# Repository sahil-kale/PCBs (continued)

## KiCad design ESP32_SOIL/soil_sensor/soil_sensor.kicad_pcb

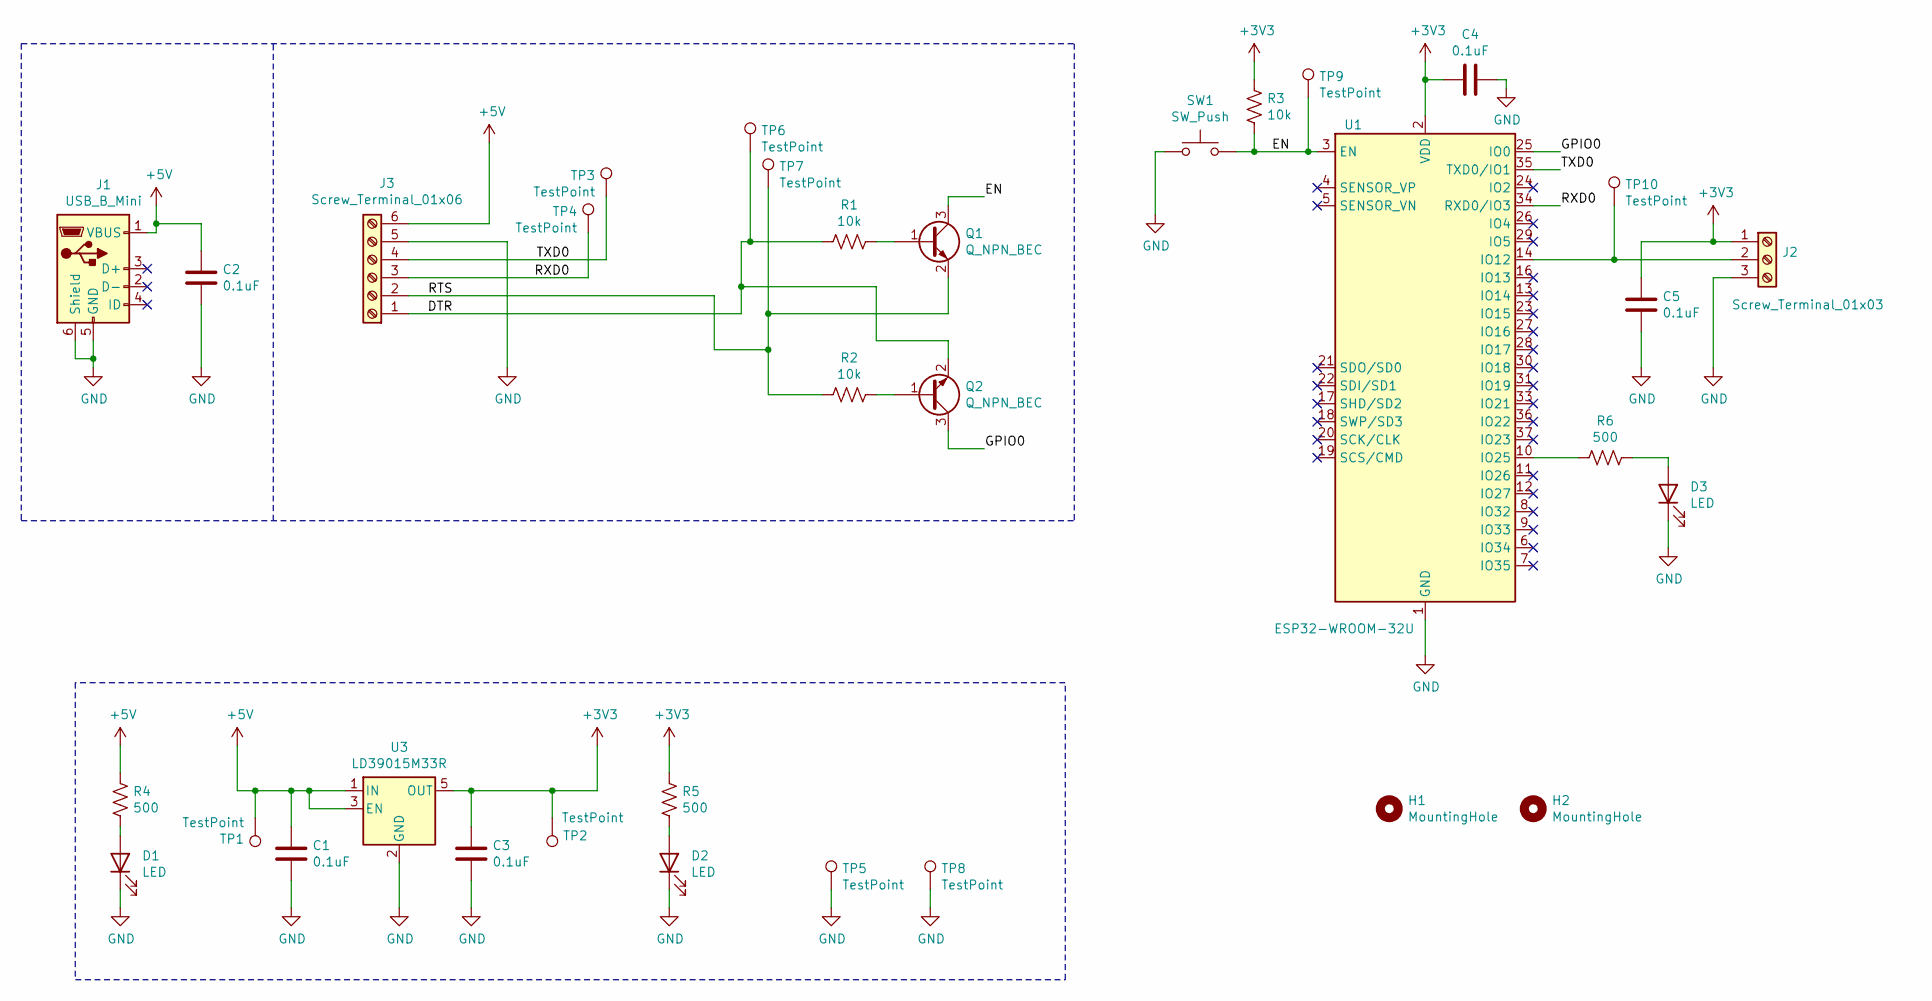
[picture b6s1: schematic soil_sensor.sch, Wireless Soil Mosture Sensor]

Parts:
C1, C2, C3, C4, C5: 0.1uF; C_0603_1608Metric_Pad1.08x0.95mm_HandSolder; Digikey 311-1824-1-ND
D1: LED; LED_0603_1608Metric_Pad1.05x0.95mm_HandSolder; Digikey P14141CT-ND
D2: LED; LED_0603_1608Metric_Pad1.05x0.95mm_HandSolder; Digikey 732-4978-1-ND
D3: LED; LED_0603_1608Metric_Pad1.05x0.95mm_HandSolder; Digikey 732-4980-1-ND
H1, H2: MountingHole; MountingHole_2.1mm
J1: USB_B_Mini; USB_Micro-B_Molex_47346-0001; Digikey WM17141CT-ND
J2: Screw_Terminal_01x03; TerminalBlock_Phoenix_PT-1,5-3-5.0-H_1x03_P5.00mm_Horizontal; Digikey 277-1578-ND
J3: Screw_Terminal_01x06; PinSocket_1x06_P2.54mm_Vertical; Digikey 1849-PR20204VBNN-ND
Q1: Q_NPN_BEC; SOT-23; Digikey 641-1790-1-ND
Q2: Q_NPN_BEC; SOT-23; Digikey FMMTL619TADICT-ND
R1, R2, R3: 10k; R_0603_1608Metric_Pad0.98x0.95mm_HandSolder; Digikey RMCF0603JG10K0CT-ND
R4, R5, R6: 500; R_0603_1608Metric_Pad0.98x0.95mm_HandSolder; Digikey CR0603-FX-7500ELFCT-ND
SW1: SW_Push; SW_PUSH-12mm_Wuerth-430476085716; Digikey 430476085716-ND
TP1, TP2, TP3, TP4, TP5, TP6, TP7, TP8, TP9, TP10: TestPoint; TestPoint_Pad_D1.0mm
U1: ESP32-WROOM-32U; Digikey 1904-1007-1-ND
U3: LD39015M33R; SOT-23-5; Digikey 497-6979-1-ND

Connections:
+3V3: C3.2, C4.2, C5.2, J2.1, R3.1, R5.1, TP2.1, U1.2 (VDD), U3.5 (OUT)
+5V: C1.2, C2.2, J1.1 (VBUS), J3.6, R4.1, TP1.1, U3.1 (IN), U3.3 (EN)
/DTR: J3.1, Q2.2 (E), R1.2, TP6.1
/EN: Q1.3 (C), R3.2, SW1.2, TP9.1, U1.3 (EN)
/GPIO0: Q2.3 (C), U1.25 (IO0)
/RTS: J3.2, Q1.2 (E), R2.2, TP7.1
/RXD0: J3.3, TP4.1, U1.34 (RXD0/IO3)
/TXD0: J3.4, TP3.1, U1.35 (TXD0/IO1)
GND: C1.1, C2.1, C3.1, C4.1, C5.1, D1.1 (K), D2.1 (K), D3.1 (K), J1.5 (GND), J1.6 (Shield), J2.3, J3.5, SW1.1, TP5.1, TP8.1, U1.1 (GND), U1.15 (GND), U1.38 (GND), U1.39 (GND), U3.2 (GND)
unnamed: D1.2 (A), R4.2
unnamed: D2.2 (A), R5.2
unnamed: D3.2 (A), R6.1
unnamed: J2.2, TP10.1, U1.14 (IO12)
unnamed: Q1.1 (B), R1.1
unnamed: Q2.1 (B), R2.1
unnamed: R6.2, U1.10 (IO25)

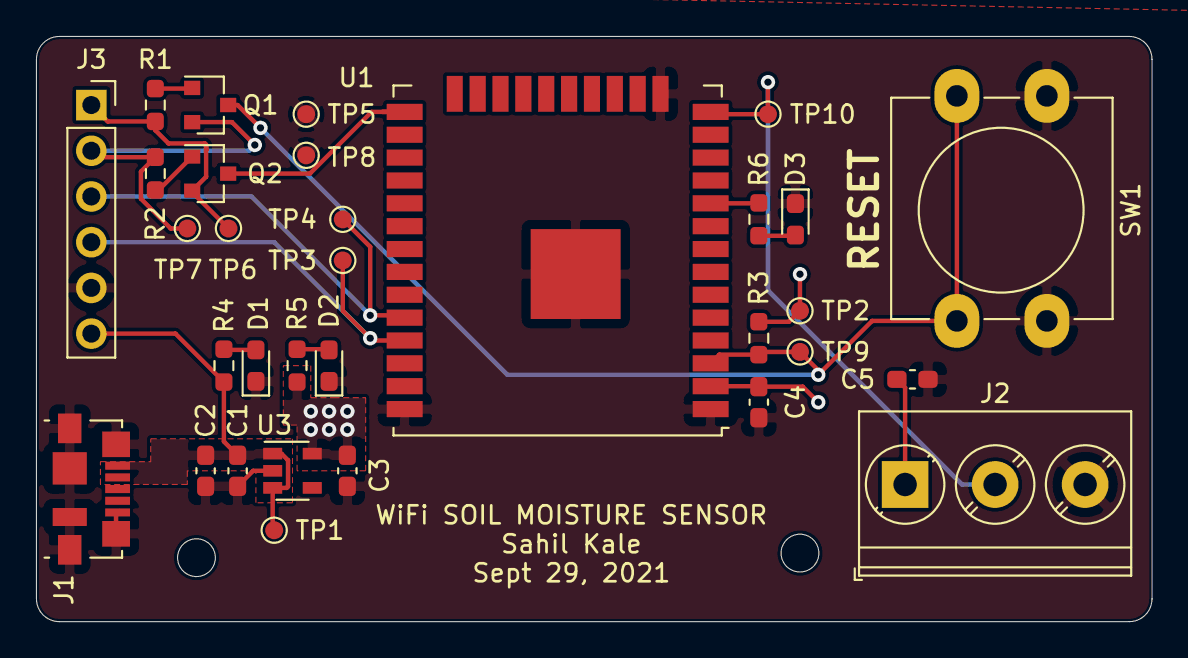
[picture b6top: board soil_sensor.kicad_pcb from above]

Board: 2 copper layers, 62.0 x 32.5 mm, 34 parts (0 on the bottom side), 16 nets.

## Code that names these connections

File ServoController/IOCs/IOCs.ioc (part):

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Mcu.Name=STM32L431C(B-C)Tx
Mcu.Package=LQFP48
Mcu.UserName=STM32L431CCTx
PA0.GPIOParameters=GPIO_Label
PA0.GPIO_Label=CURR_A
PA0.Signal=ADCx_IN5
PA1.GPIOParameters=GPIO_Label
PA1.GPIO_Label=CURR_B
PA1.Signal=ADCx_IN6
PA10.Mode=Asynchronous
PA10.Signal=USART1_RX
PA13\ (JTMS-SWDIO).Mode=Trace_Asynchronous_SW
PA13\ (JTMS-SWDIO).Signal=SYS_JTMS-SWDIO
PA14\ (JTCK-SWCLK).Mode=Trace_Asynchronous_SW
PA14\ (JTCK-SWCLK).Signal=SYS_JTCK-SWCLK
PA5.GPIOParameters=GPIO_Label
PA5.GPIO_Label=PWM_IN
PA5.Signal=S_TIM2_CH1
PA6.GPIOParameters=GPIO_Label
PA6.GPIO_Label=DIR_A
PA6.Signal=GPIO_Output
PA7.GPIOParameters=GPIO_Label
PA7.GPIO_Label=DIR_B
PA7.Signal=GPIO_Output
PA8.GPIOParameters=GPIO_Label
PA8.GPIO_Label=PWM_A
PA8.Signal=S_TIM1_CH1
PA9.GPIOParameters=GPIO_Label
PA9.GPIO_Label=PWM_B
PA9.Signal=S_TIM1_CH2
PB0.GPIOParameters=GPIO_Label
PB0.GPIO_Label=FAULT_A
PB0.Signal=GPIO_Input
PB1.GPIOParameters=GPIO_Label
PB1.GPIO_Label=FAULT_B
PB1.Signal=GPIO_Input
PB10.GPIOParameters=GPIO_Label
PB10.GPIO_Label=SLEEP_B
PB10.Signal=GPIO_Output
PB12.GPIOParameters=GPIO_Label
PB12.GPIO_Label=BRAKE_A
PB12.Signal=GPIO_Output
PB13.GPIOParameters=GPIO_Label
PB13.GPIO_Label=BRAKE_B
PB13.Signal=GPIO_Output
PB2.GPIOParameters=GPIO_Label
PB2.GPIO_Label=SLEEP_A
PB2.Signal=GPIO_Output
PB3\ (JTDO-TRACESWO).Mode=Trace_Asynchronous_SW
PB3\ (JTDO-TRACESWO).Signal=SYS_JTDO-SWO
PB6.Mode=Asynchronous
PB6.Signal=USART1_TX
PB7.GPIOParameters=GPIO_Label
PB7.GPIO_Label=UART_RESET
PB7.Signal=GPIO_Output
PB8.GPIOParameters=GPIO_Label
PB8.GPIO_Label=LED2
PB8.Signal=GPIO_Output
PB9.GPIOParameters=GPIO_Label
PB9.GPIO_Label=LED1
PB9.Signal=GPIO_Output
PH0-OSC_IN\ (PH0).Mode=HSE-External-Clock-Source
PH0-OSC_IN\ (PH0).Signal=RCC_OSC_IN
RCC.HSE_VALUE=40000000
board=custom

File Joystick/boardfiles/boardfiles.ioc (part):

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Mcu.Name=STM32L151C(6-8-B)Tx
Mcu.Package=LQFP48
Mcu.UserName=STM32L151CBTx
PA11.Mode=Device
PA11.Signal=USB_DM
PA12.Mode=Device
PA12.Signal=USB_DP
PA13.Mode=Trace_Asynchronous_SW
PA13.Signal=SYS_JTMS-SWDIO
PA14.Mode=Trace_Asynchronous_SW
PA14.Signal=SYS_JTCK-SWCLK
PA3.GPIOParameters=GPIO_Label
PA3.GPIO_Label=ADC_RESET
PA3.Signal=GPIO_Output
PA4.GPIOParameters=GPIO_Label
PA4.GPIO_Label=ADC_CS
PA4.Signal=GPIO_Output
PA5.Mode=Full_Duplex_Master
PA5.Signal=SPI1_SCK
PA6.Mode=Full_Duplex_Master
PA6.Signal=SPI1_MISO
PA7.Mode=Full_Duplex_Master
PA7.Signal=SPI1_MOSI
PB0.GPIOParameters=GPIO_Label
PB0.GPIO_Label=ADC_DRDY
PB0.Signal=GPIO_Input
PB10.Signal=GPIO_Input
PB11.Signal=GPIO_Input
PB12.Signal=GPIO_Input
PB13.Signal=GPIO_Input
PB14.Signal=GPIO_Input
PB3.Mode=Trace_Asynchronous_SW
PB3.Signal=SYS_JTDO-TRACESWO
PB5.GPIOParameters=GPIO_Label
PB5.GPIO_Label=LCD_RESET
PB5.Signal=GPIO_Output
PB6.Mode=I2C
PB6.Signal=I2C1_SCL
PB7.Mode=I2C
PB7.Signal=I2C1_SDA
PB8.Signal=GPIO_Input
PB9.Signal=GPIO_Input
PH0-OSC_IN.Mode=HSE-External-Clock-Source
PH0-OSC_IN.Signal=RCC_OSC_IN
RCC.HSE_VALUE=24000000
RCC.SYSCLKFreq_VALUE=16000000
RCC.SYSCLKSource=RCC_SYSCLKSOURCE_HSI
board=custom

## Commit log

2020-12-07 Add Photo
2020-12-07 Rename Atmel_Ice_Breakout_Readme.md to readme.md
2021-01-13 Add in libs
2021-01-21 Update SCHLIB
2021-02-13 Commit LED Tron patch
2021-02-14 Create PDF outputs
2021-02-15 Commit existing changes
2021-02-21 Add in gerbers for Patch
2021-03-08 Update Schematic
2021-03-08 Add in generic op-amp
2021-04-26 Add in RGB LED
2021-04-26 Add in CUSTOM AWOS project
2021-04-27 More work on Custom AWOS
2021-04-29 Rename
2021-04-29 Update components
2021-04-30 Start Layout
2021-04-30 Add in silkscreen labels
2021-04-30 Add in pin headers
2021-04-30 Start routing
2021-05-05 Better Layout 2.0
2021-05-05 Layout almost complete
2021-05-05 More layout tings
2021-05-05 Finish first draft
2021-05-07 Finish semi-final draft
2021-05-08 Replace LDO
2021-05-08 Switch to AVR
2021-05-09 Make gerbers
2021-06-07 Add in PDF
2021-06-21 Add in more PWM generation stuff from KiCAD
2021-06-28 Add in gerbers
2021-07-18 Add in LT Spice stuff
2021-07-18 Rename readme.md to README.md
2021-09-28 CustomESC stuff
2021-09-30 Add in soil sensor stuff
2021-10-10 Add in Boost Converter
2021-10-10 Create simple STM32 breakout
2021-10-11 Initial Project
2021-10-14 Add in boost Converter and STM32 Breakout
2021-10-18 Minor changes to ESP32 schematic
2021-10-23 A few changes here and there
2021-10-24 Finish Custom ESC layout
2021-10-24 Add in schematic
2021-11-20 More Stuff
2022-06-19 random stuff for custom esc
2022-06-19 Create joystick project
2022-06-20 Make draft schematic
2022-08-28 Update joystick files
2022-09-22 commit random
2023-02-12 ServoController
